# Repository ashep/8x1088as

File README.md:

# 8x1088AS LED Matrix Board

## Notes

The 1088AS 3D model has been taken from [aniline](https://github.com/aniline/akn.3dshapes). All the credit goes to the author.

## Changelog

### 2024-11-17

Initial release.

## Authors

- [Oleksandr Shepetko](https://shepetko.com) -- initial work.

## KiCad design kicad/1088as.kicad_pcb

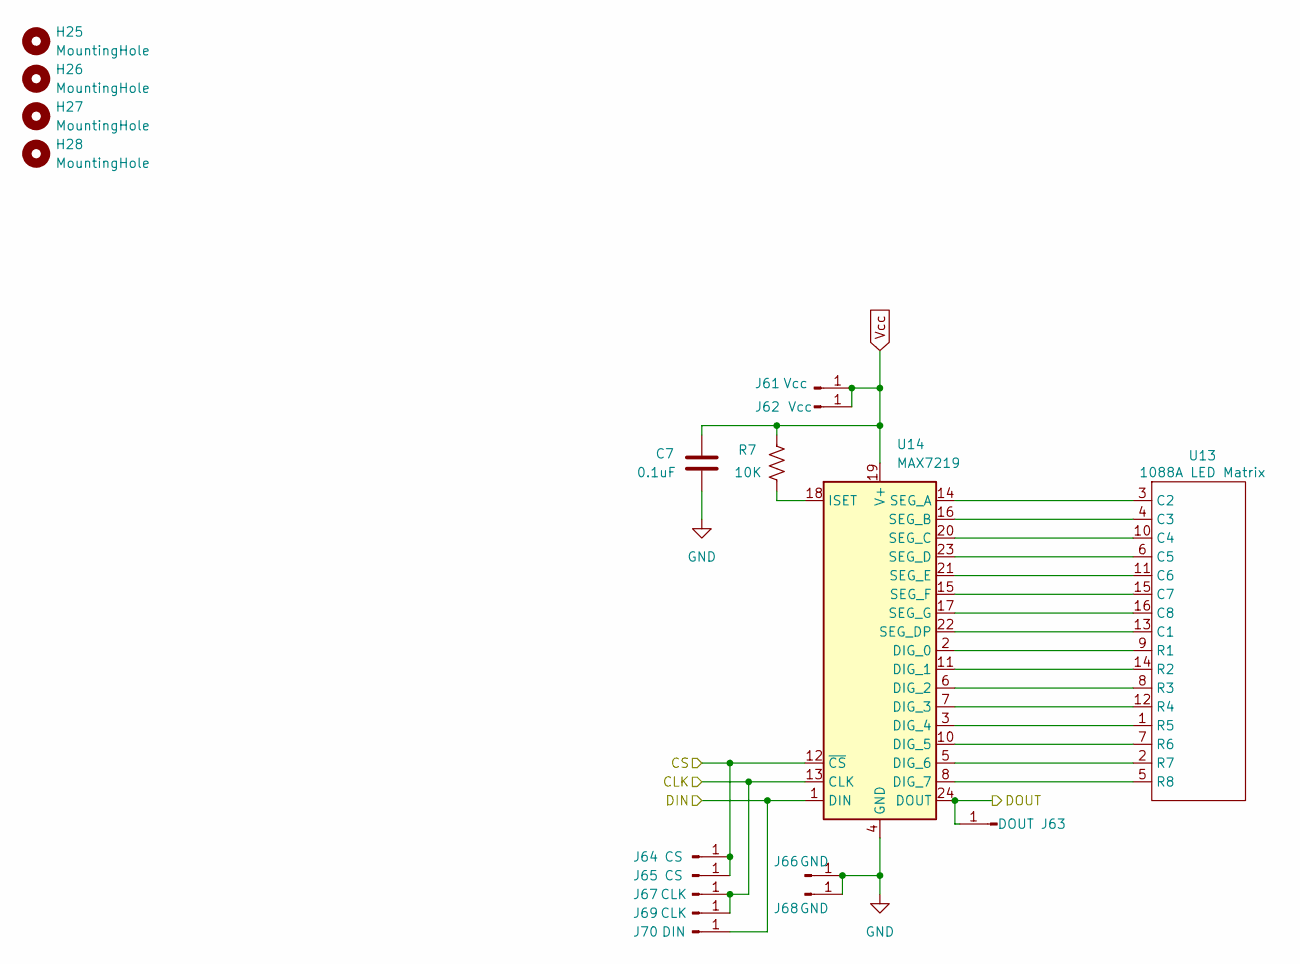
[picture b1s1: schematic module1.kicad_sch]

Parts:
C7: 0.1uF; C_1206_3216Metric_Pad1.33x1.80mm_HandSolder
H25, H26, H27, H28: MountingHole; MountingHole_3.2mm_M3
J61, J62: Vcc; PinHeader_1x01_P2.54mm_Vertical
J63: DOUT; PinHeader_1x01_P2.54mm_Vertical
J64, J65: CS; PinHeader_1x01_P2.54mm_Vertical
J66, J68: GND; PinHeader_1x01_P2.54mm_Vertical
J67, J69: CLK; PinHeader_1x01_P2.54mm_Vertical
J70: DIN; PinHeader_1x01_P2.54mm_Vertical
R7: 10K; R_1206_3216Metric_Pad1.30x1.75mm_HandSolder
U13: 1088A LED Matrix
U14: MAX7219; SOIC-24W_7.5x15.4mm_P1.27mm

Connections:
/Module1/CLK: J67.1, J69.1, U14.13 (CLK); also elsewhere on the board
/Module1/CS: J64.1, J65.1, U14.12 (~CS); also elsewhere on the board
/Module6/DOUT: J70.1, U14.1 (DIN); also elsewhere on the board
/Module7/DOUT: J63.1, U14.24 (DOUT); also elsewhere on the board
GND: C7.2, J66.1, J68.1, U14.4 (GND), U14.9 (GND); also elsewhere on the board
unnamed: U13.13 (C1), U14.22 (SEG_DP)
unnamed: U13.3 (C2), U14.14 (SEG_A)
unnamed: U13.4 (C3), U14.16 (SEG_B)
unnamed: U13.10 (C4), U14.20 (SEG_C)
unnamed: U13.6 (C5), U14.23 (SEG_D)
unnamed: U13.11 (C6), U14.21 (SEG_E)
unnamed: U13.15 (C7), U14.15 (SEG_F)
unnamed: U13.16 (C8), U14.17 (SEG_G)
unnamed: U13.9 (R1), U14.2 (DIG_0)
unnamed: U13.14 (R2), U14.11 (DIG_1)
unnamed: U13.8 (R3), U14.6 (DIG_2)
unnamed: U13.12 (R4), U14.7 (DIG_3)
unnamed: U13.1 (R5), U14.3 (DIG_4)
unnamed: U13.7 (R6), U14.10 (DIG_5)
unnamed: U13.2 (R7), U14.5 (DIG_6)
unnamed: U13.5 (R8), U14.8 (DIG_7)
unnamed: R7.2, U14.18 (ISET)
Vcc: C7.1, J61.1, J62.1, R7.1, U14.19 (V+); also elsewhere on the board

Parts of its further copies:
C1, C2, C3, C4, C5, C6, C8: 0.1uF; C_1206_3216Metric_Pad1.33x1.80mm_HandSolder
H1, H2, H3, H4, H5, H6, H7, H8, H9, H10, H11, H12, H13, H14, H15, H16, H17, H18, H19, H20, H21, H22, H23, H24, H29, H30, H31, H32: MountingHole; MountingHole_3.2mm_M3
J1, J2, J11, J12, J21, J22, J31, J32, J41, J42, J51, J52, J71, J72: Vcc; PinHeader_1x01_P2.54mm_Vertical
J3, J13, J23, J33, J43, J53, J73: DOUT; PinHeader_1x01_P2.54mm_Vertical
J4, J5, J14, J15, J24, J25, J34, J35, J44, J45, J54, J55, J74, J75: CS; PinHeader_1x01_P2.54mm_Vertical
J6, J8, J16, J18, J26, J28, J36, J38, J46, J48, J56, J58, J76, J78: GND; PinHeader_1x01_P2.54mm_Vertical
J7, J9, J17, J19, J27, J29, J37, J39, J47, J49, J57, J59, J77, J79: CLK; PinHeader_1x01_P2.54mm_Vertical
J10, J20, J30, J40, J50, J60, J80: DIN; PinHeader_1x01_P2.54mm_Vertical
R1, R2, R3, R4, R5, R6, R8: 10K; R_1206_3216Metric_Pad1.30x1.75mm_HandSolder
U1, U3, U5, U7, U9, U11, U15: 1088A LED Matrix
U2, U4, U6, U8, U10, U12, U16: MAX7219; SOIC-24W_7.5x15.4mm_P1.27mm

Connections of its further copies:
/Module1/CLK: J7.1, J9.1, J17.1, J19.1, J27.1, J29.1, J37.1, J39.1, J47.1, J49.1, J57.1, J59.1, J77.1, J79.1, U2.13 (CLK), U4.13 (CLK), U6.13 (CLK), U8.13 (CLK), U10.13 (CLK), U12.13 (CLK), U16.13 (CLK); also elsewhere on the board
/Module1/CS: J4.1, J5.1, J14.1, J15.1, J24.1, J25.1, J34.1, J35.1, J44.1, J45.1, J54.1, J55.1, J74.1, J75.1, U2.12 (~CS), U4.12 (~CS), U6.12 (~CS), U8.12 (~CS), U10.12 (~CS), U12.12 (~CS), U16.12 (~CS); also elsewhere on the board
/Module1/DIN: J10.1, U2.1 (DIN)
/Module1/DOUT: J3.1, J20.1, U2.24 (DOUT), U4.1 (DIN)
/Module2/DOUT: J13.1, J30.1, U4.24 (DOUT), U6.1 (DIN)
/Module3/DOUT: J23.1, J40.1, U6.24 (DOUT), U8.1 (DIN)
/Module4/DOUT: J33.1, J50.1, U8.24 (DOUT), U10.1 (DIN)
/Module5/DOUT: J43.1, J60.1, U10.24 (DOUT), U12.1 (DIN)
/Module6/DOUT: J53.1, U12.24 (DOUT); also elsewhere on the board
/Module7/DOUT: J80.1, U16.1 (DIN); also elsewhere on the board
/Module8/DOUT: J73.1, U16.24 (DOUT)
GND: C1.2, C2.2, C3.2, C4.2, C5.2, C6.2, C8.2, J6.1, J8.1, J16.1, J18.1, J26.1, J28.1, J36.1, J38.1, J46.1, J48.1, J56.1, J58.1, J76.1, J78.1, U2.4 (GND), U2.9 (GND), U4.4 (GND), U4.9 (GND), U6.4 (GND), U6.9 (GND), U8.4 (GND), U8.9 (GND), U10.4 (GND), U10.9 (GND), U12.4 (GND), U12.9 (GND), U16.4 (GND), U16.9 (GND); also elsewhere on the board
unnamed: U1.13 (C1), U2.22 (SEG_DP)
unnamed: U1.3 (C2), U2.14 (SEG_A)
unnamed: U1.4 (C3), U2.16 (SEG_B)
unnamed: U1.10 (C4), U2.20 (SEG_C)
unnamed: U1.6 (C5), U2.23 (SEG_D)
unnamed: U1.11 (C6), U2.21 (SEG_E)
unnamed: U1.15 (C7), U2.15 (SEG_F)
unnamed: U1.16 (C8), U2.17 (SEG_G)
unnamed: U1.9 (R1), U2.2 (DIG_0)
unnamed: U1.14 (R2), U2.11 (DIG_1)
unnamed: U1.8 (R3), U2.6 (DIG_2)
unnamed: U1.12 (R4), U2.7 (DIG_3)
unnamed: U1.1 (R5), U2.3 (DIG_4)
unnamed: U1.7 (R6), U2.10 (DIG_5)
unnamed: U1.2 (R7), U2.5 (DIG_6)
unnamed: U1.5 (R8), U2.8 (DIG_7)
unnamed: R1.2, U2.18 (ISET)
unnamed: U3.13 (C1), U4.22 (SEG_DP)
unnamed: U3.3 (C2), U4.14 (SEG_A)
unnamed: U3.4 (C3), U4.16 (SEG_B)
unnamed: U3.10 (C4), U4.20 (SEG_C)
unnamed: U3.6 (C5), U4.23 (SEG_D)
unnamed: U3.11 (C6), U4.21 (SEG_E)
unnamed: U3.15 (C7), U4.15 (SEG_F)
unnamed: U3.16 (C8), U4.17 (SEG_G)
unnamed: U3.9 (R1), U4.2 (DIG_0)
unnamed: U3.14 (R2), U4.11 (DIG_1)
unnamed: U3.8 (R3), U4.6 (DIG_2)
unnamed: U3.12 (R4), U4.7 (DIG_3)
unnamed: U3.1 (R5), U4.3 (DIG_4)
unnamed: U3.7 (R6), U4.10 (DIG_5)
unnamed: U3.2 (R7), U4.5 (DIG_6)
unnamed: U3.5 (R8), U4.8 (DIG_7)
unnamed: R2.2, U4.18 (ISET)
unnamed: U5.13 (C1), U6.22 (SEG_DP)
unnamed: U5.3 (C2), U6.14 (SEG_A)
unnamed: U5.4 (C3), U6.16 (SEG_B)
unnamed: U5.10 (C4), U6.20 (SEG_C)
unnamed: U5.6 (C5), U6.23 (SEG_D)
unnamed: U5.11 (C6), U6.21 (SEG_E)
unnamed: U5.15 (C7), U6.15 (SEG_F)
unnamed: U5.16 (C8), U6.17 (SEG_G)
unnamed: U5.9 (R1), U6.2 (DIG_0)
unnamed: U5.14 (R2), U6.11 (DIG_1)
unnamed: U5.8 (R3), U6.6 (DIG_2)
unnamed: U5.12 (R4), U6.7 (DIG_3)
unnamed: U5.1 (R5), U6.3 (DIG_4)
unnamed: U5.7 (R6), U6.10 (DIG_5)
unnamed: U5.2 (R7), U6.5 (DIG_6)
unnamed: U5.5 (R8), U6.8 (DIG_7)
unnamed: R3.2, U6.18 (ISET)
unnamed: U7.13 (C1), U8.22 (SEG_DP)
unnamed: U7.3 (C2), U8.14 (SEG_A)
unnamed: U7.4 (C3), U8.16 (SEG_B)
unnamed: U7.10 (C4), U8.20 (SEG_C)
unnamed: U7.6 (C5), U8.23 (SEG_D)
unnamed: U7.11 (C6), U8.21 (SEG_E)
unnamed: U7.15 (C7), U8.15 (SEG_F)
unnamed: U7.16 (C8), U8.17 (SEG_G)
unnamed: U7.9 (R1), U8.2 (DIG_0)
unnamed: U7.14 (R2), U8.11 (DIG_1)
unnamed: U7.8 (R3), U8.6 (DIG_2)
unnamed: U7.12 (R4), U8.7 (DIG_3)
unnamed: U7.1 (R5), U8.3 (DIG_4)
unnamed: U7.7 (R6), U8.10 (DIG_5)
unnamed: U7.2 (R7), U8.5 (DIG_6)
unnamed: U7.5 (R8), U8.8 (DIG_7)
unnamed: R4.2, U8.18 (ISET)
unnamed: U9.9 (R1), U10.2 (DIG_0)
unnamed: U9.14 (R2), U10.11 (DIG_1)
unnamed: U9.8 (R3), U10.6 (DIG_2)
unnamed: U9.12 (R4), U10.7 (DIG_3)
unnamed: U9.1 (R5), U10.3 (DIG_4)
unnamed: U9.7 (R6), U10.10 (DIG_5)
unnamed: U9.2 (R7), U10.5 (DIG_6)
unnamed: U9.5 (R8), U10.8 (DIG_7)
unnamed: R5.2, U10.18 (ISET)
unnamed: U9.3 (C2), U10.14 (SEG_A)
unnamed: U9.4 (C3), U10.16 (SEG_B)
unnamed: U9.10 (C4), U10.20 (SEG_C)
unnamed: U9.6 (C5), U10.23 (SEG_D)
unnamed: U9.13 (C1), U10.22 (SEG_DP)
unnamed: U9.11 (C6), U10.21 (SEG_E)
unnamed: U9.15 (C7), U10.15 (SEG_F)
unnamed: U9.16 (C8), U10.17 (SEG_G)
unnamed: U11.13 (C1), U12.22 (SEG_DP)
unnamed: U11.3 (C2), U12.14 (SEG_A)
unnamed: U11.4 (C3), U12.16 (SEG_B)
unnamed: U11.10 (C4), U12.20 (SEG_C)
unnamed: U11.6 (C5), U12.23 (SEG_D)
unnamed: U11.11 (C6), U12.21 (SEG_E)
unnamed: U11.15 (C7), U12.15 (SEG_F)
unnamed: U11.16 (C8), U12.17 (SEG_G)
unnamed: U11.9 (R1), U12.2 (DIG_0)
unnamed: U11.14 (R2), U12.11 (DIG_1)
unnamed: U11.8 (R3), U12.6 (DIG_2)
unnamed: U11.12 (R4), U12.7 (DIG_3)
unnamed: U11.1 (R5), U12.3 (DIG_4)
unnamed: U11.7 (R6), U12.10 (DIG_5)
unnamed: U11.2 (R7), U12.5 (DIG_6)
unnamed: U11.5 (R8), U12.8 (DIG_7)
unnamed: R6.2, U12.18 (ISET)
unnamed: U15.13 (C1), U16.22 (SEG_DP)
unnamed: U15.3 (C2), U16.14 (SEG_A)
unnamed: U15.4 (C3), U16.16 (SEG_B)
unnamed: U15.10 (C4), U16.20 (SEG_C)
unnamed: U15.6 (C5), U16.23 (SEG_D)
unnamed: U15.11 (C6), U16.21 (SEG_E)
unnamed: U15.15 (C7), U16.15 (SEG_F)
unnamed: U15.16 (C8), U16.17 (SEG_G)
unnamed: U15.9 (R1), U16.2 (DIG_0)
unnamed: U15.14 (R2), U16.11 (DIG_1)
unnamed: U15.8 (R3), U16.6 (DIG_2)
unnamed: U15.12 (R4), U16.7 (DIG_3)
unnamed: U15.1 (R5), U16.3 (DIG_4)
unnamed: U15.7 (R6), U16.10 (DIG_5)
unnamed: U15.2 (R7), U16.5 (DIG_6)
unnamed: U15.5 (R8), U16.8 (DIG_7)
unnamed: R8.2, U16.18 (ISET)
Vcc: C1.1, C2.1, C3.1, C4.1, C5.1, C6.1, C8.1, J1.1, J2.1, J11.1, J12.1, J21.1, J22.1, J31.1, J32.1, J41.1, J42.1, J51.1, J52.1, J71.1, J72.1, R1.1, R2.1, R3.1, R4.1, R5.1, R6.1, R8.1, U2.19 (V+), U4.19 (V+), U6.19 (V+), U8.19 (V+), U10.19 (V+), U12.19 (V+), U16.19 (V+); also elsewhere on the board

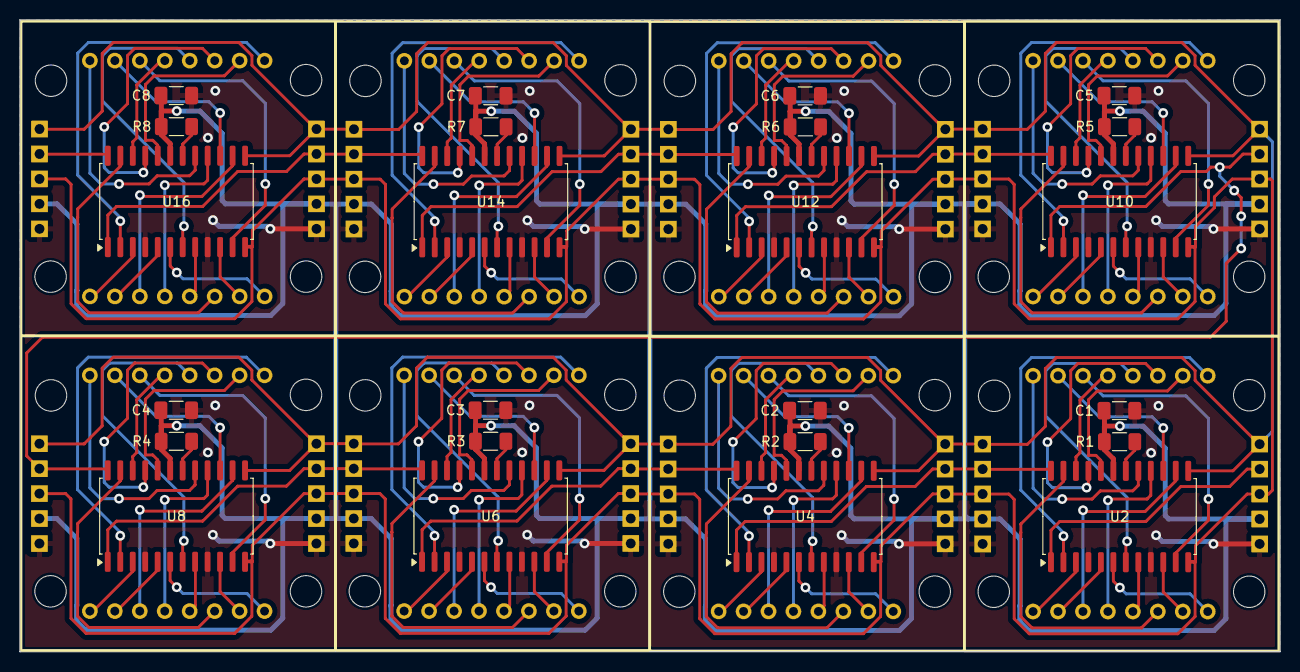
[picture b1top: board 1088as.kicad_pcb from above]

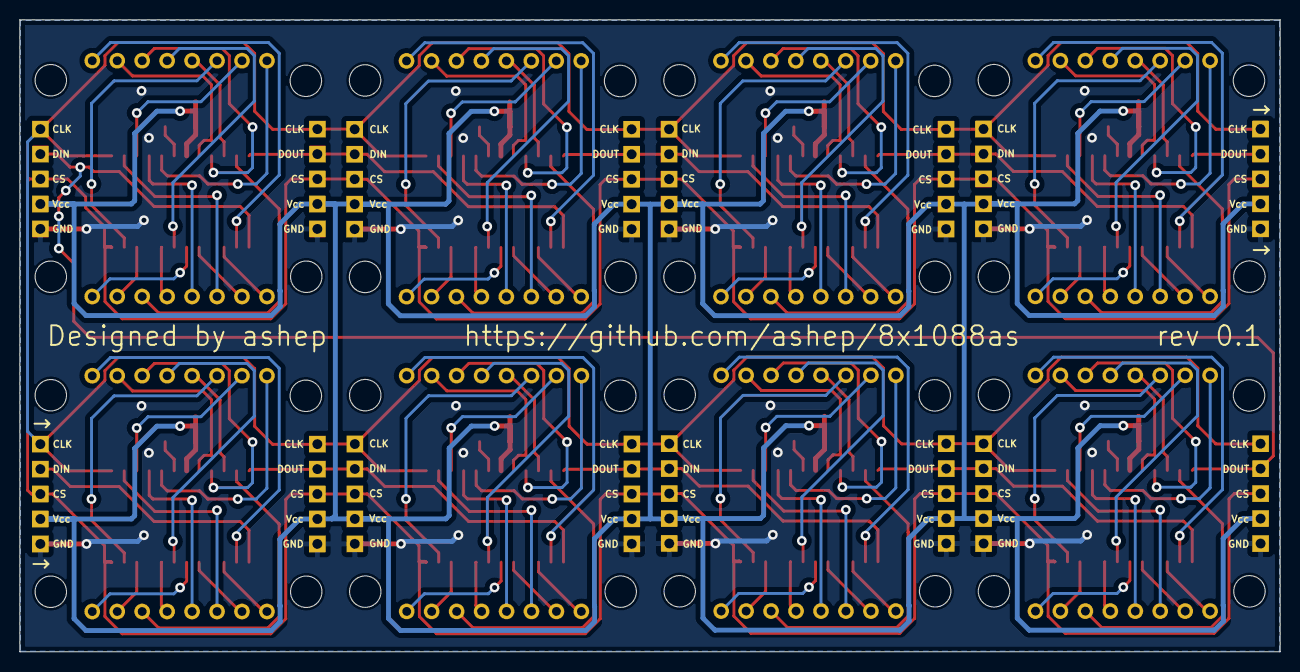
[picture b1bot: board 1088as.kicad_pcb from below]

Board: 2 copper layers, 128.3 x 64.3 mm, 144 parts (80 on the bottom side), 149 nets.

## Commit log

2024-11-17 First release
